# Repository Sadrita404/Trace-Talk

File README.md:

<div align="center">
  <table border="0" cellpadding="0" cellspacing="0">
    <tr>
      <td align="center" style="background: #ffffff; border: 1px solid #d0d7de; border-radius: 12px; padding: 16px; box-shadow: 0 4px 12px rgba(0,0,0,0.05);">
        
        <div style="margin-top: 12px; font-family: -apple-system, BlinkMacSystemFont, 'Segoe UI', Helvetica, Arial, sans-serif; font-size: 13px; color: #57606a; font-weight: 500;">
      </td>
    </tr>
  </table>
</div>

| Title | Trace Talk |
| :-- | :---|
|Author |Sadrita Neogi|

## What's this?

TraceTalk is a walkie-talkie small radio  powered by a custom PCB and an ATMEGA328P (Arduino) microcontroller. It features a built-in rechargeable battery that charges with any standard USB-C cable and power brick. I also put together a custom enclosure to keep the PCB safe.
## Why I built it ?

From a very starting point, I walkie talkie due to their principle of work like the transmission between two devices without any internet connection and we are able to talk to each other. This made me fascinated, and I also wanted to make one for myself, but in general, the walkie-talkie that we see is balki and heavy so I made it pocket size, slim, walkie-talkie that can be connected via headphone and we can use it.

## How to use ?

To use the walkie-talkie, just plug any headphones with a mic into the 3.5mm jack, then flip the switch on the left side of the board and the LED will turn on. Just press and hold the button on the board to transmit your voice, and any nearby walkie-talkies will pick it up and play the audio. No pairing or setup needed.

The battery will lasts for about 4 hours( according to my calculation that I have made by going to the data sheet of each components, and this is what I approximately estimated ) and charges with any USB-C cable and power source. While it's charging, an LED near the USB port will light up, and it'll turn off once the battery is fully charged. Just a heads-up: the headphones you use can affect the audio quality, so you might want to try a few different pairs to see what works best.

## Technical Description
This project runs on an ATMEGA328P microcontroller sitting on a custom PCB (TraceTalk). It sends all the audio data through an NRF24L01 radio module. The ATMEGA328P runs at 3.3V and 8MHz, and you can program it right through the Arduino IDE. While you could technically use an external programmer like a USBTinyISP, the Arduino IDE is definitely the easiest and most straightforward way to go.

For the radio, I used the SMD version of the NRF24L01 to keep the board as small as possible. It gets a maximum range of about 100 meters.

The LiPo battery is soldered straight onto the board's battery terminals. I’d recommend picking up a battery with a 100-150mAh capacity—that’s the sweet spot for getting the best results.

<div align="center">

| | Building Process | |
| :---: | :---: | :---: |
|  |  |  |
|  |  |  |
|  |  |  |

<div align="center">
  <h2> Final Look </h2>
  <table border="0" cellpadding="10" cellspacing="0" style="border-collapse: collapse;">
    <tr>
      <!-- FRONT SIDE CARD -->
      <td align="center" valign="top" width="50%" style="background: #ffffff; border: 1px solid #d0d7de; border-radius: 12px; padding: 16px; box-shadow: 0 4px 12px rgba(0,0,0,0.05);">
        
        <div style="margin-top: 12px; font-family: -apple-system, BlinkMacSystemFont, 'Segoe UI', Helvetica, Arial, sans-serif; font-size: 13px; color: #57606a; font-weight: 600; text-transform: uppercase; letter-spacing: 0.5px;">
          ▲ Front Side View
        </div>
      </td>
      <!-- SPACER FOR GITHUB MOBILE DEGRADATION -->
      <td width="2%">&nbsp;</td>
      <!-- BACK SIDE CARD -->
      <td align="center" valign="top" width="50%" style="background: #ffffff; border: 1px solid #d0d7de; border-radius: 12px; padding: 16px; box-shadow: 0 4px 12px rgba(0,0,0,0.05);">
        
        <div style="margin-top: 12px; font-family: -apple-system, BlinkMacSystemFont, 'Segoe UI', Helvetica, Arial, sans-serif; font-size: 13px; color: #57606a; font-weight: 600; text-transform: uppercase; letter-spacing: 0.5px;">
          ▲ Back Side View
        </div>
      </td>
    </tr>
  </table>
</div>
</div>

<div align="center">
  <h2> Bill of Materials </h2>
</div>

| Name | Purpose | Qty | Total (USD) | Link | Distributor |
| :--- | :--- | :---: | :---: | :---: | :--- |
| PCBA SMT Assembly | SMT assembly of all SMD components | 5 | 51.93 | — | JLCPCB |
| PCB Fabrication (Trace Talk) | 2-layer PCB — the board itself | 5 | 2.00 | — | JLCPCB |
| C10,C11,C3 | 100nF 50V X7R ±10% 0805 MLCC | 25 | 0.87 | [Link](https://lcsc.com/product-detail/C476766.html) | JLCPCB |
| D1,D2 | Red Water Clear 0805 LED Indication | 22 | 0.31 | [Link](https://lcsc.com/product-detail/C434431.html) | JLCPCB |
| J1 | 1A 3.5mm Headphone Jack 30V SMD R/A | 6 | 0.63 | [Link](https://lcsc.com/product-detail/C521460.html) | JLCPCB |
| J2 | 0.3mm 1mm 5P Right Angle Top Contact FFC/FPC Connector | 6 | 0.59 | [Link](https://lcsc.com/product-detail/C262360.html) | JLCPCB |
| R1,R5,R6 | 330Ω 125mW 150V Thick Film Resistor ±5% 0805 | 25 | 0.07 | [Link](https://lcsc.com/product-detail/C25306.html) | JLCPCB |
| R2,R3 | 5.1kΩ 125mW 150V Thick Film Resistor ±1% 0805 | 10 | 0.04 | [Link](https://lcsc.com/product-detail/C27834.html) | JLCPCB |
| R10,R4 | 1kΩ 125mW 150V Thick Film Resistor ±1% 0805 | 20 | 0.09 | [Link](https://lcsc.com/product-detail/C95781.html) | JLCPCB |
| R11,R12,R13,R7,R8,R9 | 10kΩ 125mW 150V Thick Film Resistor ±1% 0805 | 30 | 0.13 | [Link](https://lcsc.com/product-detail/C17414.html) | JLCPCB |
| C1,C2,C4,C5,C6,C8 | 10V 10uF X5R ±10% 0805 MLCC | 40 | 7.11 | [Link](https://lcsc.com/product-detail/C17024.html) | JLCPCB |
| SW1 | PCM12SMTR SPDT Surface Mount Vertical Slide Switch | 5 | 6.23 | [Link](https://lcsc.com/product-detail/C221841.html) | JLCPCB |
| SW2 | PTS645 Tactile Switches 12V 50mA SMD-4P 6x6mm | 5 | 1.53 | [Link](https://lcsc.com/product-detail/C221871.html) | JLCPCB |
| U2 | MIC5205-3.3YM5-TR Fixed 3.3V 150mA Linear LDO SOT-23-5 | 5 | 1.88 | [Link](https://lcsc.com/product-detail/C37970.html) | JLCPCB |
| U3 | TP4056X-42-ESOP8 1A 4.2V Lithium Battery Charging IC | 5 | 1.00 | [Link](https://lcsc.com/product-detail/C2763448.html) | JLCPCB |
| U4 | LM358DR2G 32V Dual Operational Amplifier SOIC-8 | 5 | 0.29 | [Link](https://lcsc.com/product-detail/C7950.html) | JLCPCB |
| U5 | ATMEGA328P-AU 8-Bit AVR 20MHz TQFP-32 Microcontroller | 5 | 11.38 | [Link](https://lcsc.com/product-detail/C14877.html) | JLCPCB |
| USB1 | USB Type-C Receptacle 16P Female SMD R/A | 5 | 0.92 | [Link](https://lcsc.com/product-detail/C165948.html) | JLCPCB |
| X1 | 8MHz 33pF SMD3213-3P Ceramic Resonator | 5 | 1.92 | [Link](https://lcsc.com/product-detail/C341522.html) | JLCPCB |
| RG1 | 470kΩ 125mW 150V Thick Film Resistor ±1% 0805 | 5 | 0.02 | [Link](https://lcsc.com/product-detail/C17709.html) | JLCPCB |
| C7,C9 | 330nF 50V X7R ±10% 0805 MLCC | 20 | 0.66 | [Link](https://lcsc.com/product-detail/C1740.html) | JLCPCB |
| 3.7V 100mAH | To power the circuit | 2 | 0.00 | [Link](https://www.electropi.in/3.7v-100mah-lipo-battery-model-321225-india) | Self Sourced |
| 3d Print | For the encloser | 1 | 0.00 | [Link](https://printlegion.hackclub.com/) | #printing-legion |
| Shipping PCB	| E- Post (Cheapest) | 	- |	$10.98	| — | 	JLCPCB |
| Total |    |     |   $100.58    |   |    |   |

**Project Under Hack Club**

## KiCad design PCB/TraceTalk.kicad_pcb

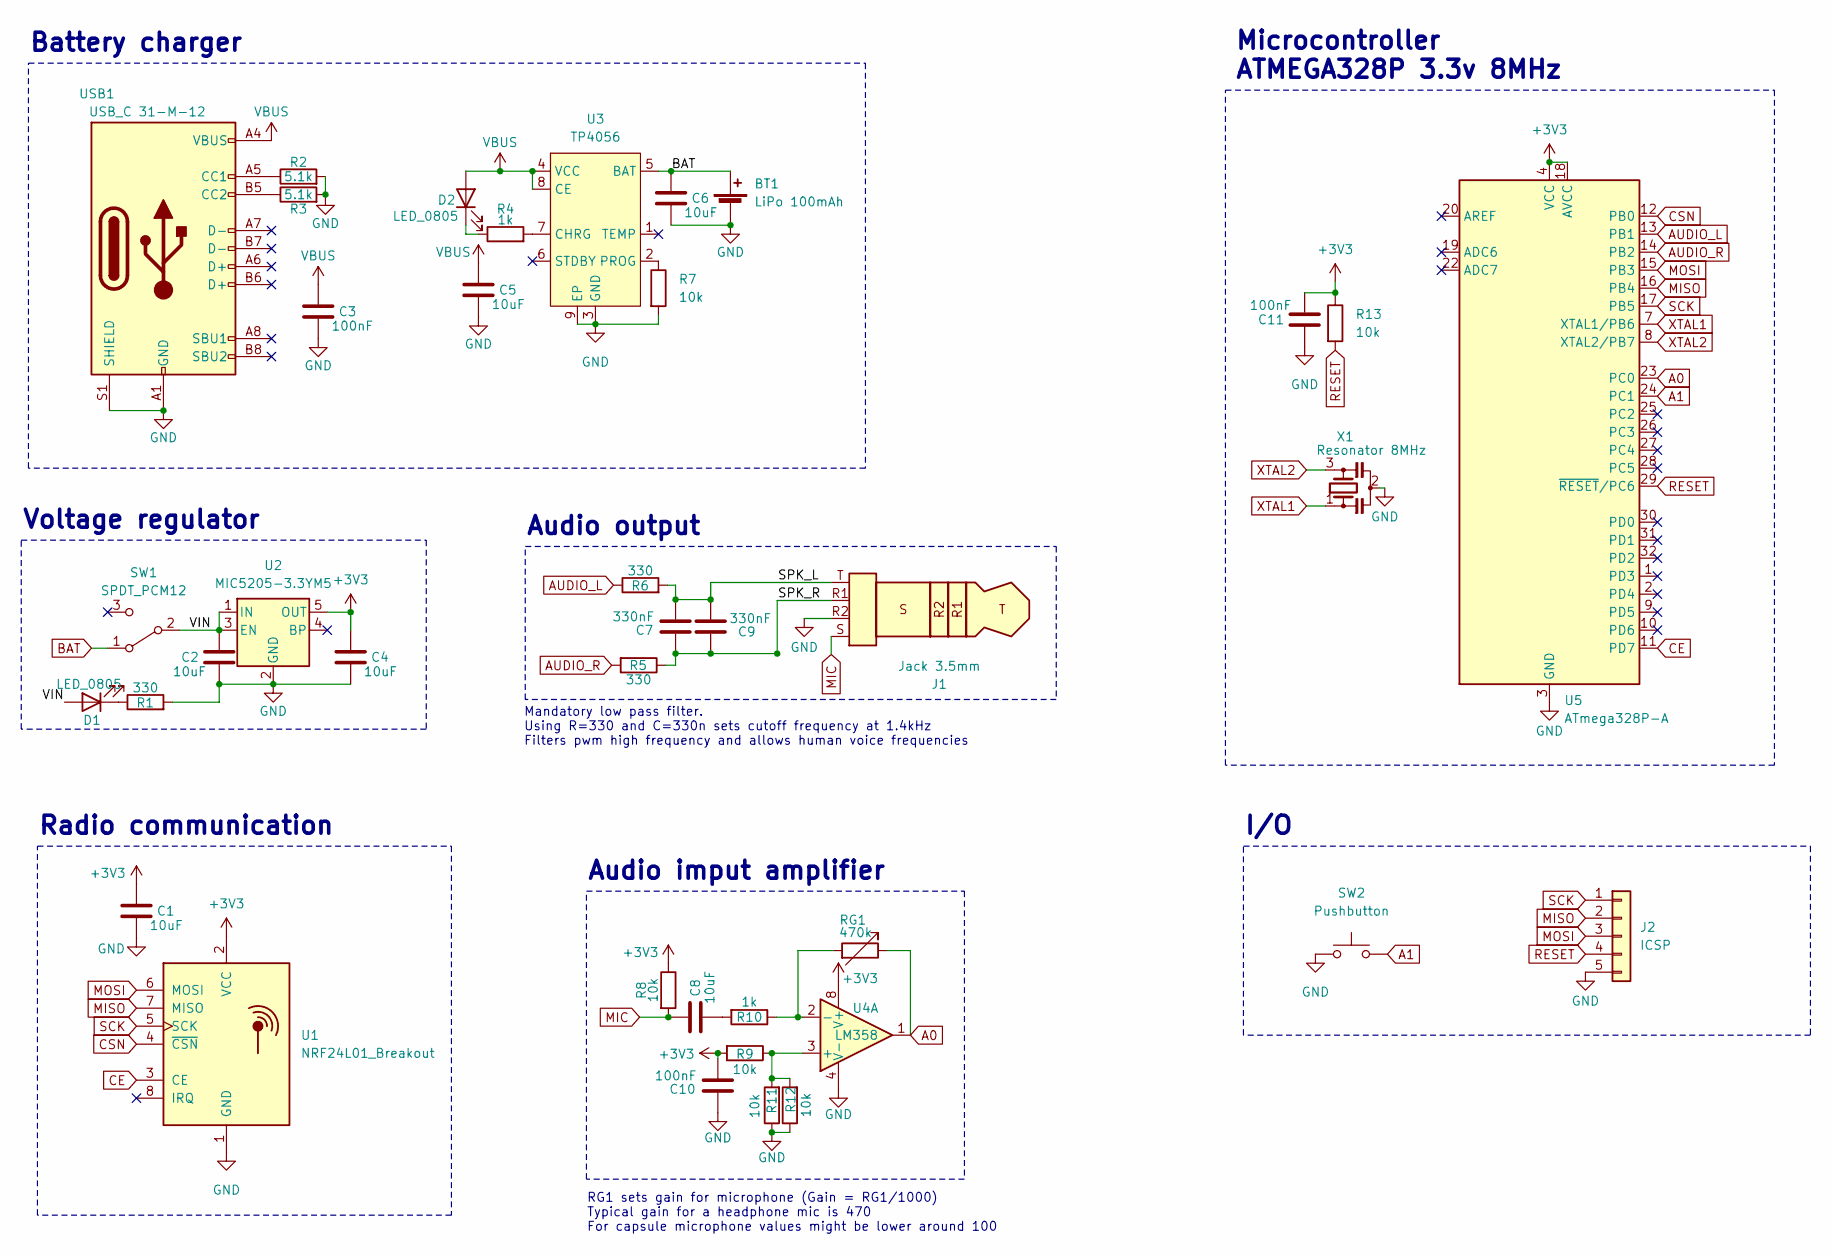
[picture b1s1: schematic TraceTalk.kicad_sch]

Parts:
BT1: LiPo 100mAh; PinSocket_1x02_P2.54mm_Vertical
C1, C2, C4, C5, C6, C8: 10uF; C_0805_2012Metric
C3, C10, C11: 100nF; C_0805_2012Metric
C7, C9: 330nF; C_0805_2012Metric
D1, D2: LED_0805; LED_0805_2012Metric
J1: Jack 3.5mm; Jack_3.5mm_PJ320D_Horizontal
J2: ICSP; Molex_200528-0050_1x05-1MP_P1.00mm_Horizontal
R1, R5, R6: 330; R_0805_2012Metric
R2, R3: 5.1k; R_0805_2012Metric
R4, R10: 1k; R_0805_2012Metric
R7, R8, R9, R11, R12, R13: 10k; R_0805_2012Metric
RG1: 470k; R_0805_2012Metric
SW1: SPDT_PCM12; SW_SPDT_PCM12
SW2: Pushbutton; SW_SPST_PTS645
U1: NRF24L01_Breakout; NRF24L01_Mini
U2: MIC5205-3.3YM5; SOT-23-5
U3: TP4056; SOIC-8-1EP_3.9x4.9mm_P1.27mm_EP2.29x3mm
U4: LM358; SOP-8_3.9x4.9mm_P1.27mm
U5: ATmega328P-A; TQFP-32_7x7mm_P0.8mm
USB1: USB_C 31-M-12; USB_C_Receptacle_HRO_TYPE-C-31-M-12
X1: Resonator 8MHz; Resonator_SMD_Murata_CSTxExxV-3Pin_3.0x1.1mm

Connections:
+3V3: C1.1, C4.1, C10.2, C11.2, R8.1, R9.2, R13.1, U1.2 (VCC), U2.5 (OUT), U4.8 (V+), U5.4 (VCC), U5.6 (VCC), U5.18 (AVCC)
/SPK_L: C7.2, C9.2, J1.T, R6.2
/SPK_R: C7.1, C9.1, J1.R1, R5.1
/VIN: C2.1, D1.2 (A), SW1.2 (B), U2.1 (IN), U2.3 (EN)
A0: RG1.1, U4.1, U5.23 (PC0)
A1: SW2.2, U5.24 (PC1)
AUDIO_L: R6.1, U5.13 (PB1)
AUDIO_R: R5.2, U5.14 (PB2)
BAT: BT1.1 (+), C6.1, SW1.1 (A), U3.5 (BAT)
CE: U1.3 (CE), U5.11 (PD7)
CSN: U1.4 (~CSN), U5.12 (PB0)
GND: BT1.2 (-), C1.2, C2.2, C3.2, C4.2, C5.2, C6.2, C10.1, C11.1, J1.R2, J2.5, R1.2, R2.2, R3.2, R7.2, R11.1, R12.1, SW2.1, U1.1 (GND), U2.2 (GND), U3.3 (GND), U3.9 (EP), U4.4 (V-), U5.3 (GND), U5.5 (GND), U5.21 (GND), USB1.A1 (GND), USB1.A12 (GND), USB1.B1 (GND), USB1.B12 (GND), USB1.S1 (SHIELD), X1.2
MIC: C8.1, J1.S, R8.2
MISO: J2.2, U1.7 (MISO), U5.16 (PB4)
MOSI: J2.3, U1.6 (MOSI), U5.15 (PB3)
unnamed: C8.2, R10.2
unnamed: D1.1 (K), R1.1
unnamed: D2.1 (K), R4.1
unnamed: R2.1, USB1.A5 (CC1)
unnamed: R3.1, USB1.B5 (CC2)
unnamed: R4.2, U3.7 (CHRG)
unnamed: R7.1, U3.2 (PROG)
unnamed: R10.1, RG1.2, U4.2 (-)
unnamed: R9.1, R11.2, R12.2, U4.3 (+)
RESET: J2.4, R13.2, U5.29 (~RESET/PC6)
SCK: J2.1, U1.5 (SCK), U5.17 (PB5)
VBUS: C3.1, C5.1, D2.2 (A), U3.4 (VCC), U3.8 (CE), USB1.A4 (VBUS), USB1.A9 (VBUS), USB1.B4 (VBUS), USB1.B9 (VBUS)
XTAL1: U5.7 (XTAL1/PB6), X1.1
XTAL2: U5.8 (XTAL2/PB7), X1.3

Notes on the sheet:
Battery charger
Audio imput amplifier
Mandatory low pass filter. Using R=330 and C=330n sets cutoff frequency at 1.4kHz Filters pwm high frequency and allows human voice frequencies
I/O
RG1 sets gain for microphone (Gain = RG1/1000) Typical gain for a headphone mic is 470 For capsule microphone values might be lower around 100
Radio communication
Microcontroller ATMEGA328P 3.3v 8MHz
Audio output
Voltage regulator

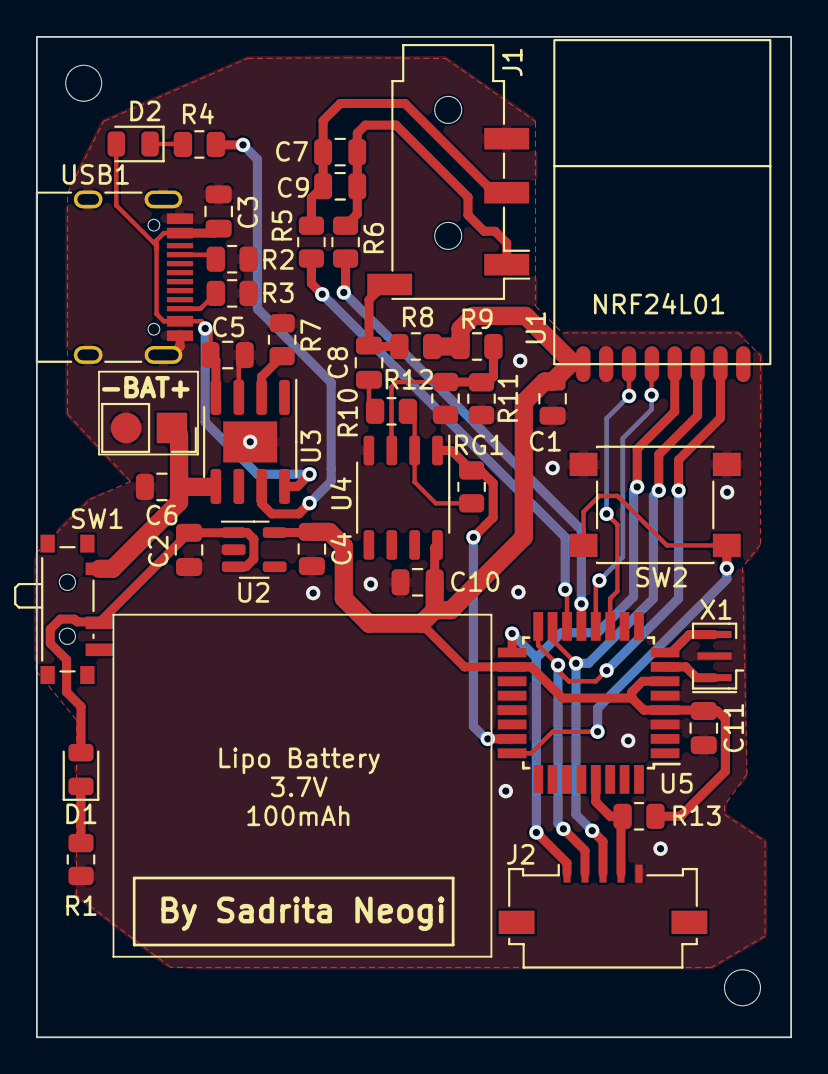
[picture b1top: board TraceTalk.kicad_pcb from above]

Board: 2 copper layers, 41.9 x 55.6 mm, 39 parts (0 on the bottom side), 29 nets.

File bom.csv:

Name,Purpose,Quantity,Total Cost (USD),Link,Distributor
"PCBA SMT Assembly","SMT assembly of all SMD components",5,51.93,"","JLCPCB"
"PCB Fabrication (Trace Talk)","2-layer PCB — the board itself",5,2.00,"","JLCPCB"
"C10,C11,C3","100nF 50V X7R ±10% 0805 MLCC",25,0.87,"https://lcsc.com/product-detail/C476766.html","JLCPCB"
"D1,D2","Red Water Clear 0805 LED Indication",22,0.31,"https://lcsc.com/product-detail/C434431.html","JLCPCB"
"J1","1A 3.5mm Headphone Jack 30V SMD R/A",6,0.63,"https://lcsc.com/product-detail/C521460.html","JLCPCB"
"J2","0.3mm 1mm 5P Right Angle Top Contact FFC/FPC Connector",6,0.59,"https://lcsc.com/product-detail/C262360.html","JLCPCB"
"R1,R5,R6","330Ω 125mW 150V Thick Film Resistor ±5% 0805",25,0.07,"https://lcsc.com/product-detail/C25306.html","JLCPCB"
"R2,R3","5.1kΩ 125mW 150V Thick Film Resistor ±1% 0805",10,0.04,"https://lcsc.com/product-detail/C27834.html","JLCPCB"
"R10,R4","1kΩ 125mW 150V Thick Film Resistor ±1% 0805",20,0.09,"https://lcsc.com/product-detail/C95781.html","JLCPCB"
"R11,R12,R13,R7,R8,R9","10kΩ 125mW 150V Thick Film Resistor ±1% 0805",30,0.13,"https://lcsc.com/product-detail/C17414.html","JLCPCB"
"C1,C2,C4,C5,C6,C8","10V 10uF X5R ±10% 0805 MLCC",40,7.11,"https://lcsc.com/product-detail/C17024.html","JLCPCB"
"SW1","PCM12SMTR SPDT Surface Mount Vertical Slide Switch",5,6.23,"https://lcsc.com/product-detail/C221841.html","JLCPCB"
"SW2","PTS645 Tactile Switches 12V 50mA SMD-4P 6x6mm",5,1.53,"https://lcsc.com/product-detail/C221871.html","JLCPCB"
"U2","MIC5205-3.3YM5-TR Fixed 3.3V 150mA Linear LDO SOT-23-5",5,1.88,"https://lcsc.com/product-detail/C37970.html","JLCPCB"
"U3","TP4056X-42-ESOP8 1A 4.2V Lithium Battery Charging IC",5,1.00,"https://lcsc.com/product-detail/C2763448.html","JLCPCB"
"U4","LM358DR2G 32V Dual Operational Amplifier SOIC-8",5,0.29,"https://lcsc.com/product-detail/C7950.html","JLCPCB"
"U5","ATMEGA328P-AU 8-Bit AVR 20MHz TQFP-32 Microcontroller",5,11.38,"https://lcsc.com/product-detail/C14877.html","JLCPCB"
"USB1","USB Type-C Receptacle 16P Female SMD R/A",5,0.92,"https://lcsc.com/product-detail/C165948.html","JLCPCB"
"X1","8MHz 33pF SMD3213-3P Ceramic Resonator",5,1.92,"https://lcsc.com/product-detail/C341522.html","JLCPCB"
"RG1","470kΩ 125mW 150V Thick Film Resistor ±1% 0805",5,0.02,"https://lcsc.com/product-detail/C17709.html","JLCPCB"
"C7,C9","330nF 50V X7R ±10% 0805 MLCC",20,0.66,"https://lcsc.com/product-detail/C1740.html","JLCPCB"

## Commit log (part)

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2026-06-29 kicad file added
2026-06-29 jlc production
